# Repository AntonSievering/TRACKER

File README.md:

# TRACKER - Sounding Rocket Tracking and Positioning Project

The rocket carries a transmitter that continuously downlinks telemetry along with timing signals. Multiple ground receivers (3–4 planned) receive the signal and extract the timing information. With the timing data, the system computes the rocket’s position in real time.

This repository contains the PCB projects for TRACKER
- GPSDO-V2: 10 MHz oscillator tuned by the GPS timing signals
  
- basestation-rx: S-band timing signal receiver
  
- tracker-tx-fpga: FPGA baseboard with three subcarrier slots
  
- tracker-subcarrier-adc: ADC subcarrier for FPGA baseboard
  
- tracker-subcarrier-dac: DAC subcarrier for FPGA baseboard
  
- tracker-tx: RF Upconverter for the rocket-side transmitter (untested)

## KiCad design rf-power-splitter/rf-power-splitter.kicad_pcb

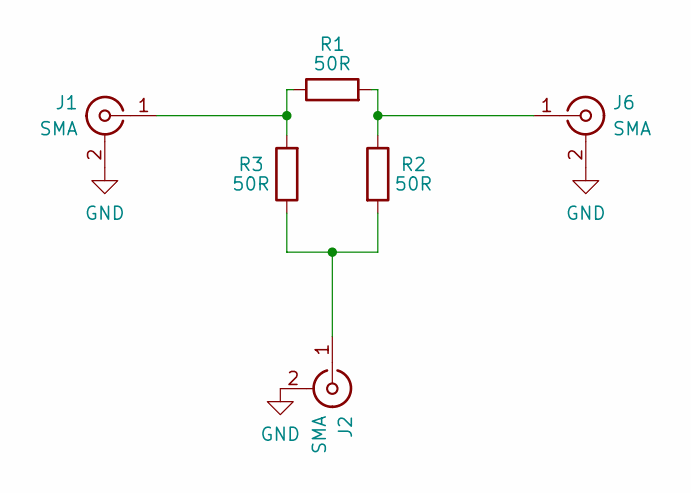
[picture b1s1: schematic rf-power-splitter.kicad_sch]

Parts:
J1, J2, J6: SMA; SMA_Edge_Mount
R1, R2, R3: 50R; R_0402_1005Metric; MPN FC0402E50R0BST1

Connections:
GND: J1.2 (Ext), J2.2 (Ext), J6.2 (Ext)
unnamed: J1.1 (In), R1.1, R3.2
unnamed: J2.1 (In), R2.2, R3.1
unnamed: J6.1 (In), R1.2, R2.1

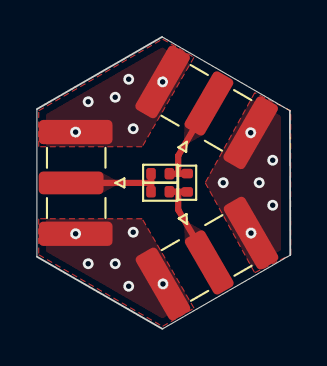
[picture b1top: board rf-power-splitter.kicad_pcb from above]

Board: 4 copper layers, 14.1 x 16.2 mm, 6 parts (0 on the bottom side), 4 nets.

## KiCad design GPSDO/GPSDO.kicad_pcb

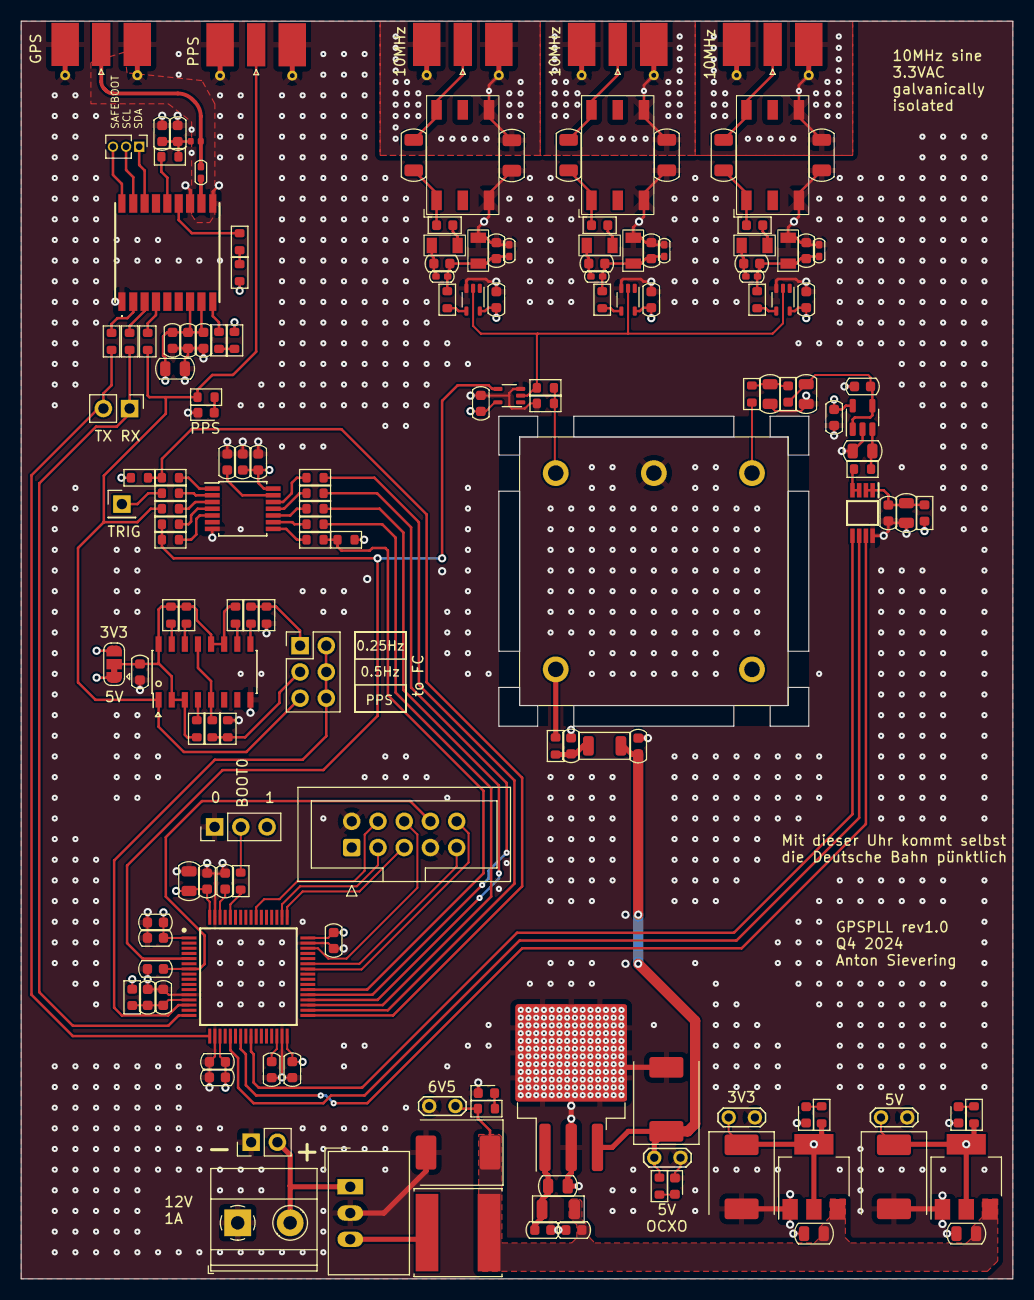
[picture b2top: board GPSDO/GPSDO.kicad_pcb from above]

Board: 4 copper layers, 96.0 x 121.7 mm, 163 parts (0 on the bottom side), 105 nets.

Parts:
C1: 47p; C_0402_1005Metric_Pad0.74x0.62mm
C2: 100p; C_0603_1608Metric
C3: 10n; C_0603_1608Metric
C4, C33, C36, C39, C61, C63: 1u; C_0603_1608Metric
C5, C6, C12, C13, C18, C23, C24, C28, C29, C30, C31, C32, C35, C38, C46, C53, C62, C64: 100n; C_0603_1608Metric
C7, C21, C42, C60: 100u; CP_EIA-7361-438_AVX-U
C8, C10, C11, C25: 470n; C_0603_1608Metric
C9, C15, C16, C17, C19, C20, C22, C34, C41: 10u; C_0805_2012Metric
C14, C48, C55: 470p; C_0402_1005Metric_Pad0.74x0.62mm
C26, C27: 2u2; C_0603_1608Metric
C37, C50, C57: 56p; C_0402_1005Metric_Pad0.74x0.62mm
C40, C43, C47, C49, C54, C56: Tuning; C_0603_1608Metric
C44, C45, C51, C52, C58, C59: 100p; C_1206_3216Metric
D1, D2, D3, D4, D5: LED; LED_0603_1608Metric
FB1, FB2: 600@100MHz; L_1206_3216Metric
FB3, FB4, FB5, FB6, FB7, FB8: 1k@100MHz; L_0603_1608Metric
IC1: MAX-M10S-00B; MAXM10S00B
IC2: STM32H562RGT6; QFP50P1200X1200X160-64N
J1, J7, J8, J9, J12: SMA; SMA_Molex_73251-2120_EdgeMount_Horizontal
J2: Screw_Terminal_01x02; TerminalBlock_Phoenix_MKDS-1,5-2-5.08_1x02_P5.08mm_Horizont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
J3, J13: Conn_01x02_Pin; PinHeader_1x02_P2.54mm_Vertical
J4: Conn_01x03_Pin; PinHeader_1x03_P1.27mm_Vertical
J5: Conn_01x03; PinHeader_1x03_P2.54mm_Vertical
J6: Conn_02x05_Counter_Clockwise; IDC-Header_2x05_P2.54mm_Vertical
J10: Conn_01x01_Pin; PinHeader_1x01_P2.54mm_Vertical
J11: Conn_02x03_Odd_Even; PinHeader_2x03_P2.54mm_Vertical
JP1: SolderJumper_3_Bridged12; SolderJumper-3_P1.3mm_Bridged12_RoundedPad1.0x1.5mm
L1: 27n; L_0402_1005Metric
L2, L4, L6: 560n; NLV25-EF
L3, L5, L7: 4u7; NLV25-EF
L8: 10u; L_Changjiang_FNR8050S
R1, R2, R3, R4, R5: 33R; R_0603_1608Metric
R6, R7, R10, R11, R12, R19, R20, R21, R22, R23, R24, R27, R28, R29, R30, R31, R32, R33, R34: 0; R_0603_1608Metric
R8, R9, R35, R37, R39, R40, R41, R42: 10k; R_0603_1608Metric
R13, R15, R16: 50; R_0603_1608Metric
R14: 1k; R_0603_1608Metric
R17, R18, R25, R26: 100k; R_0603_1608Metric
R36, R38: 20k; R_0603_1608Metric
T1, T2, T3: TG04-APL7NSNL
TP1, TP2, TP3, TP4: TestPoint_2Pole; TestPoint_2Pads_Pitch2.54mm_Drill0.8mm
U1: TSR_1-2465; Converter_DCDC_TRACO_TSR-1_THT
U2: ADC8551; SOP65P490X110-8N
U3: LM1117MP-5.0; SOT-223-3_TabPin2
U4: TL081; SOT-23-5
U5, U7, U8, U9: 74LVC1G17; Texas_R-PDSO-G5_DCK-5
U6: LM1117MP-3.3; SOT-223-3_TabPin2
U10: LM2940; TO-263-3_TabPin2
U11: TDC7200; TSSOP-14_4.4x5mm_P0.65mm
U12: 74VHC112; SOIC-16_3.9x9.9mm_Pitch1.27mm
X1: OC5SC25

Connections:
+3.3V: C4.1, C5.1, C6.1, C12.1, C13.1, C17.1, C28.1, C29.1, C30.1, C31.1, C33.1, C34.1, C38.1, C39.1, C42.1, C46.1, C53.1, C62.1, C63.1, FB8.2, IC1.7 (V_IO), IC1.8 (VCC), IC2.1 (VBAT), IC2.19 (VDD_1), IC2.32 (VDD_2), IC2.48 (VDD_3), IC2.64 (VDD_4), J5.3, J6.1, JP1.3 (B), R17.1, R18.1, R25.1, R26.1, R39.1, TP1.1, U5.5 (VCC), U6.2 (VO), U7.5 (VCC), U8.5 (VCC), U9.5 (VCC), U11.14 (V_{DD})
+5V: C21.1, C24.1, FB7.1, JP1.1 (A), R40.1, TP2.1, U3.2 (VO), U4.5 (V+)
+12V: J2.2, J3.2, U1.1 (Vin)
/DAC/adc_amp+: C22.1, R8.2, U4.3 (+)
/DAC/adc_vdd: C18.1, C19.1, FB7.2, U2.1 (V_{DD}), U2.2 (V_{REF})
/DAC/dac_vout: R8.1, U2.3 (V_{FB}), U2.4 (V_{OUT})
/DAC/vout: C15.1, C23.1, FB3.1, U4.1, U4.4 (-)
/DAC/~SYNC: IC2.25 (PC5), U2.5 (~SYNC)
/GPS/RF: C1.1, J1.1 (In), L1.1
/GPS/gps_lna_en: R5.1, R26.2
/GPS/gps_lna_en_r: IC1.13 (LNA_EN), R5.2
/GPS/gps_pps: J11.5, J12.1 (In), R3.1, R9.1, R28.1, U12.1 (CLK)
/GPS/gps_pps_r: IC1.4 (TIMEPULSE), R3.2
/GPS/gps_rxd: IC2.16 (PA2), J13.1, R2.1
/GPS/gps_rxd_r: IC1.3 (RXD), R2.2
/GPS/gps_scl_tp: IC1.17 (SCL), J4.2
/GPS/gps_sda_tp: IC1.16 (SDA), J4.1
/GPS/gps_txd: IC2.17 (PA3), J13.2, R1.1
/GPS/gps_txd_r: IC1.2 (TXD), R1.2
/GPS/gps_~reset: R4.1, R25.2
/GPS/gps_~reset_r: IC1.9 (RESET_N), R4.2
/GPS/gps_~safeboot: IC1.18 (SAFEBOOT_N), J4.3
/GPS/vcc_rf_r: IC1.14 (VCC_RF), R6.1
/Microcontroller/DAC.MOSI: IC2.23 (PA7), U2.7 (D_{IN})
/Microcontroller/DAC.SCLK: IC2.21 (PA5), U2.6 (SCLK)
/Microcontroller/DEBUG_RX: IC2.43 (PA10), J6.9
/Microcontroller/DEBUG_TX: IC2.42 (PA9), J6.10
/Microcontroller/Divide By Two (Four)/0.5HZ: J11.3, R35.2, R36.1
/Microcontroller/Divide By Two (Four)/0.25HZ: J11.1, R37.2, R38.1
/Microcontroller/Divide By Two (Four)/OUTPUT: IC2.14 (PA0), J11.2, J11.4, J11.6
/Microcontroller/Divide By Two (Four)/jk_supply: C64.1, JP1.2 (C), R31.2, R32.2, R33.1, R34.1, U12.2 (K), U12.3 (J), U12.11 (J), U12.12 (K), U12.16 (V_{cc})
/Microcontroller/JTCK: IC2.49 (PA14), J6.5
/Microcontroller/JTDI: IC2.50 (PA15), J6.3
/Microcontroller/JTDO: IC2.55 (PB3), J6.4
/Microcontroller/JTMS: IC2.46 (PA13), J6.6
/Microcontroller/NRST: C35.1, IC2.7 (NRST), J6.8
/Microcontroller/TDC.MISO: IC2.35 (PB14), R23.2
/Microcontroller/TDC.MOSI: IC2.36 (PB15), R22.2
/Microcontroller/TDC.SCLK: IC2.34 (PB13), R20.2
/Microcontroller/boot0: J5.2, R10.1
/Microcontroller/boot0_r: IC2.60 (BOOT0), R10.2
/Microcontroller/stm32_vdda: C32.1, C36.1, FB8.1, IC2.13 (VDDA)
/Microcontroller/stm_vcap1: C26.1, IC2.30 (VCAP_1)
/Microcontroller/stm_vcap2: C27.1, IC2.62 (VCAP_2)
/OCXO/Output Driver 1/out+: C44.1, J7.1 (In), T1.6 (SB)
/OCXO/Output Driver 1/out-: C45.1, J7.2 (Ext), T1.4 (SA)
/OCXO/Output Driver 2/out+: C51.1, J8.1 (In), T2.6 (SB)
/OCXO/Output Driver 2/out-: C52.1, J8.2 (Ext), T2.4 (SA)
/OCXO/Output Driver 3/out+: C58.1, J9.1 (In), T3.6 (SB)
/OCXO/Output Driver 3/out-: C59.1, J9.2 (Ext), T3.4 (SA)
/OCXO/ocxo_fout: R12.2, U5.2, U7.2, U8.2, U9.2
/OCXO/ocxo_fout_r: R12.1, R14.1, X1.1 (freq)
/OCXO/ocxo_vadj: R7.1, X1.3 (V_{adj})
/OCXO/ocxo_vcc: C11.1, FB1.2, R11.1
/Phase Comparator/tdc_clock: IC2.5 (PH0-OSC_IN), R29.1, R30.1, U7.4
/Phase Comparator/tdc_clock_r: R30.2, U11.5 (CLOCK)
/Phase Comparator/tdc_en: IC2.33 (PB12), R17.2, R19.2
/Phase Comparator/tdc_en_r: R19.1, U11.1 (EN)
/Phase Comparator/tdc_miso_r: R23.1, U11.9 (MISO)
/Phase Comparator/tdc_mosi_r: R22.1, U11.10 (MOSI)
/Phase Comparator/tdc_sclk_r: R20.1, U11.12 (SCLK)
/Phase Comparator/tdc_start_r: R28.2, U11.3 (START)
/Phase Comparator/tdc_stop_r: R29.2, U11.4 (STOP)
/Phase Comparator/tdc_trig: J10.1, R27.1
/Phase Comparator/tdc_trig_r: R27.2, U11.2 (TRIG)
/Phase Comparator/tdc_vreg: C61.1, U11.13 (V_{REG})
/Phase Comparator/tdc_~cs: IC2.37 (PC6), R21.2
/Phase Comparator/tdc_~cs_r: R21.1, U11.11 (~CS)
/Phase Comparator/tdc_~int: IC2.38 (PC7), R18.2, R24.2
/Phase Comparator/tdc_~int_r: R24.1, U11.8 (~INT)
/Power/6V5: C7.1, C8.1, C20.1, C41.1, FB2.1, L8.2, R42.1, TP4.1, U3.3 (VI), U6.3 (VI)
/Power/ocxo_5v: C10.1, C60.1, FB1.1, R41.1, TP3.1, U10.3 (VO)
/Power/ocxo_ldo_vin: C9.1, C25.1, FB2.2, U10.1 (VI)
GND: C2.2, C3.2, C4.2, C5.2, C6.2, C7.2, C8.2, C9.2, C10.2, C11.2, C12.2, C13.2, C14.1, C15.2, C16.2, C17.2, C18.2, C19.2, C20.2, C21.2, C22.2, C23.2, C24.2, C25.2, C26.2, C27.2, C28.2, C29.2, C30.2, C31.2, C32.2, C33.2, C34.2, C35.2, C36.2, C38.2, C39.2, C41.2, C42.2, C43.1, C45.2, C46.2, C47.1, C48.1, C52.2, C53.2, C54.1, C55.1, C59.2, C60.2, C61.2, C62.2, C63.2, C64.2, D1.1 (K), D2.1 (K), D3.1 (K), D4.1 (K), D5.1 (K), IC1.1 (GND_1), IC1.10 (GND_2), IC1.12 (GND_3), IC2.12 (VSSA), IC2.18 (VSS_1), IC2.31 (VSS_2), IC2.47 (VSS_3), IC2.63 (VSS_4), J1.2 (Ext), J2.1, J3.1, J5.1, J6.2, J6.7, J12.2 (Ext), L2.2, L4.2, L6.2, R14.2, R36.2, R38.2, T1.3 (AB), T2.3 (AB), T3.3 (AB), TP1.2, TP2.2, TP3.2, TP4.2, U1.2 (GND), U2.8 (GND), U3.1 (GND), U4.2 (V-), U5.3 (GND), U6.1 (GND), U7.3 (GND), U8.3 (GND), U9.3 (GND), U10.2 (GND), U11.7 (GND), U12.8 (GND), X1.2 (GND)
unnamed: C2.1, C3.1, L1.2, R6.2
unnamed: C14.2, C37.2, C40.2, C43.2, L2.1, R15.2
unnamed: C16.1, FB3.2, R7.2
unnamed: C37.1, C40.1, L3.1
unnamed: C47.2, C48.2, C49.2, C50.2, L4.1, R13.2
unnamed: C49.1, C50.1, L5.1
unnamed: C54.2, C55.2, C56.2, C57.2, L6.1, R16.2
unnamed: C56.1, C57.1, L7.1
unnamed: D1.2 (A), R9.2
unnamed: D2.2 (A), R39.2
unnamed: D3.2 (A), R40.2
unnamed: D4.2 (A), R41.2
unnamed: D5.2 (A), R42.2
unnamed: FB4.1, L3.2
unnamed: FB5.1, L5.2
unnamed: FB6.1, L7.2
unnamed: C1.2, IC1.11 (RF_IN)
unnamed: R13.1, U8.4
unnamed: R15.1, U5.4
unnamed: R16.1, U9.4
unnamed: C44.2, FB4.2, T1.1 (AA)
unnamed: C51.2, FB5.2, T2.1 (AA)
unnamed: C58.2, FB6.2, T3.1 (AA)
unnamed: L8.1, U1.3 (Vout)
unnamed: R35.1, U12.5 (Q), U12.13 (CLK)
unnamed: R33.2, U12.15 (~CLR)
unnamed: R31.1, U12.4 (~PR)
unnamed: R37.1, U12.9 (Q)
unnamed: R34.2, U12.14 (~CLR)
unnamed: R32.1, U12.10 (~PR)
unnamed: R11.2, X1.5 (Vcc)

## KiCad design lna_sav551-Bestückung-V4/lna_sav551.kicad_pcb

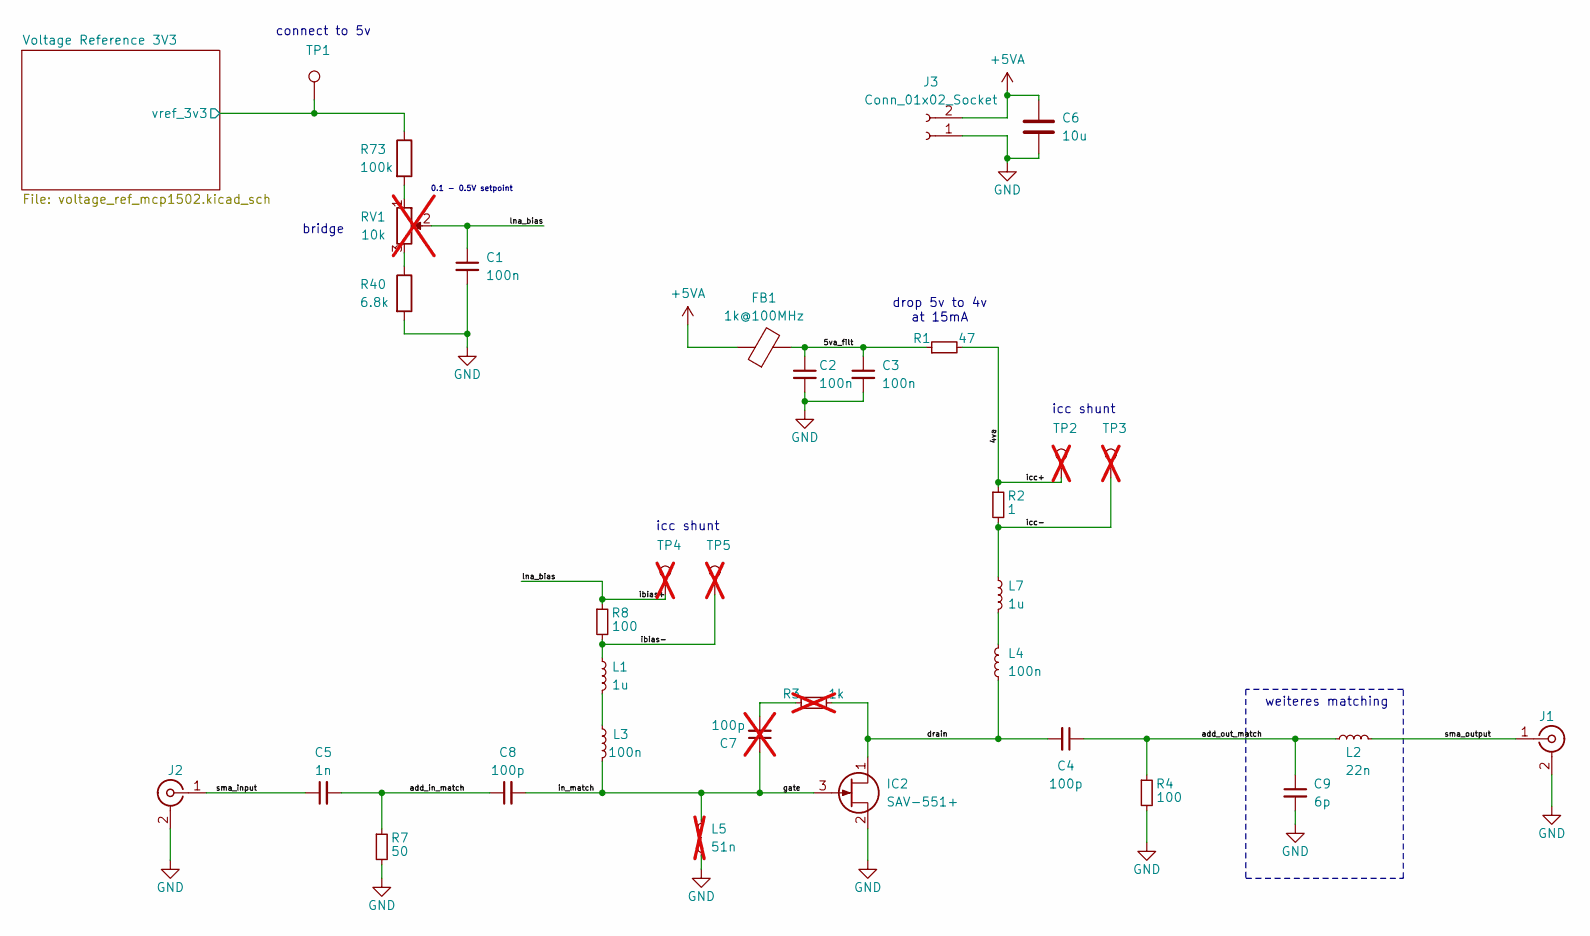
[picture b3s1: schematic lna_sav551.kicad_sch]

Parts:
C1, C2, C3: 100n; R_0603_1608Metric
C4: 100p; R_0603_1608Metric; MPN C0603C471F8HACTU
C5: 1n; R_0603_1608Metric; MPN C0603C150J8HACTU
C6: 10u; R_0805_2012Metric
C7: 100p; R_0603_1608Metric; not fitted
C8: 100p; R_0603_1608Metric; MPN C0603C150J8HACTU
C9: 6p; R_0603_1608Metric; MPN C0603C471F8HACTU
FB1: 1k@100MHz; R_0603_1608Metric; MPN 81-BLM18KG102SH1D
IC2: SAV-551+; SAV551; Manufacturer_Part_Number SAV-551+
J1, J2: SMA; SMA_Edge_Mount
J3: Conn_01x02_Socket; PinHeader_1x02_P2.54mm_Vertical
L1, L7: 1u; L_0805_2012Metric; MPN MCL2012V1-1R0-R
L2: 22n; R_0603_1608Metric; MPN AIMC-0603-82NJ-T
L3, L4: 100n; R_0603_1608Metric; MPN AIMC-0603-82NJ-T
L5: 51n; R_0603_1608Metric; MPN LQW18AN51NG00D; not fitted
R1: 47; R_0603_1608Metric
R2: 1; R_0603_1608Metric
R3: 1k; R_0603_1608Metric; not fitted
R4, R8: 100; R_0603_1608Metric
R7: 50; R_0603_1608Metric
R40: 6.8k; R_0603_1608Metric
R73: 100k; R_0603_1608Metric
RV1: 10k; Potentiometer_Bourns_3386X_Horizontal; MPN PTN10-C10HB20; not fitted
TP1: TestPoint; TestPoint_Pad_D1.0mm
TP2, TP3, TP4, TP5: TestPoint; TestPoint_Pad_D1.0mm; not fitted

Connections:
+5VA: C6.1, FB1.1, J3.2; also elsewhere on the board
/4va: R1.2, R2.1, TP2.1
/5va_filt: C2.1, C3.1, FB1.2, R1.1
/Voltage Reference 3V3/vref_3v3: R73.1, TP1.1; also elsewhere on the board
/add_in_match: C5.2, C8.1, R7.1
/add_out_match: C4.1, C9.1, L2.1, R4.1
/drain: C4.2, IC2.1, L4.1, R3.2
/gate: C7.1, C8.2, IC2.3, L3.1, L5.2
/ibias+: C1.1, R8.1, RV1.2, TP4.1
/ibias-: L1.1, R8.2, TP5.1
/icc-: L7.1, R2.2, TP3.1
/sma_input: C5.1, J2.1 (In)
/sma_output: J1.1 (In), L2.2
GND: C1.2, C2.2, C3.2, C6.2, C9.2, IC2.2, IC2.4 (GND), J1.2 (Ext), J2.2 (Ext), J3.1, L5.1, R4.2, R7.2, R40.2; also elsewhere on the board
unnamed: C7.2, R3.1
unnamed: L1.2, L3.2
unnamed: L4.2, L7.2
unnamed: R40.1, RV1.3
unnamed: R73.2, RV1.1

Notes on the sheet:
weiteres matching
drop 5v to 4v at 15mA
bridge
connect to 5v
0.1 - 0.5V setpoint
icc shunt

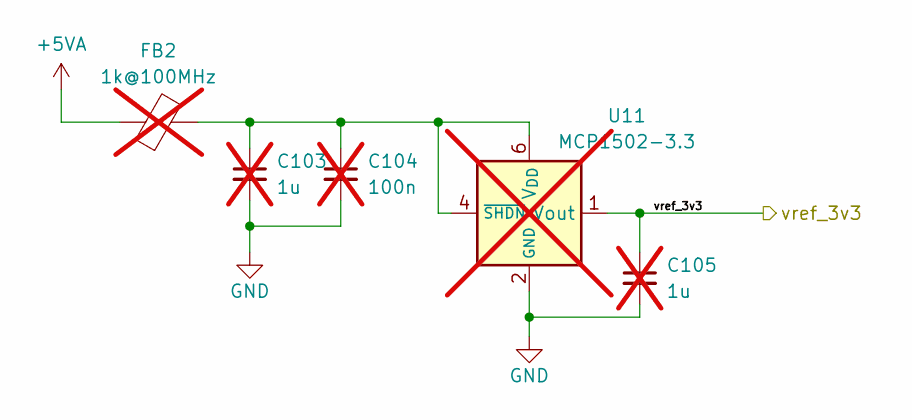
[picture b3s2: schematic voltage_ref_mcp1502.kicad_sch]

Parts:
C103, C105: 1u; R_0603_1608Metric; not fitted
C104: 100n; R_0603_1608Metric; not fitted
FB2: 1k@100MHz; R_0603_1608Metric; MPN 81-BLM18KG102SH1D; not fitted
U11: MCP1502-3.3; TSOT-23-6; MPN 579-MCP1502T-33E/CHY; not fitted

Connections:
+5VA: FB2.1; also elsewhere on the board
/Voltage Reference 3V3/vref_3v3: C105.1, U11.1 (Vout); also elsewhere on the board
GND: C103.2, C104.2, C105.2, U11.2 (GND), U11.3 (GND), U11.5 (GND); also elsewhere on the board
unnamed: C103.1, C104.1, FB2.2, U11.4 (~SHDN), U11.6 (V_{DD})

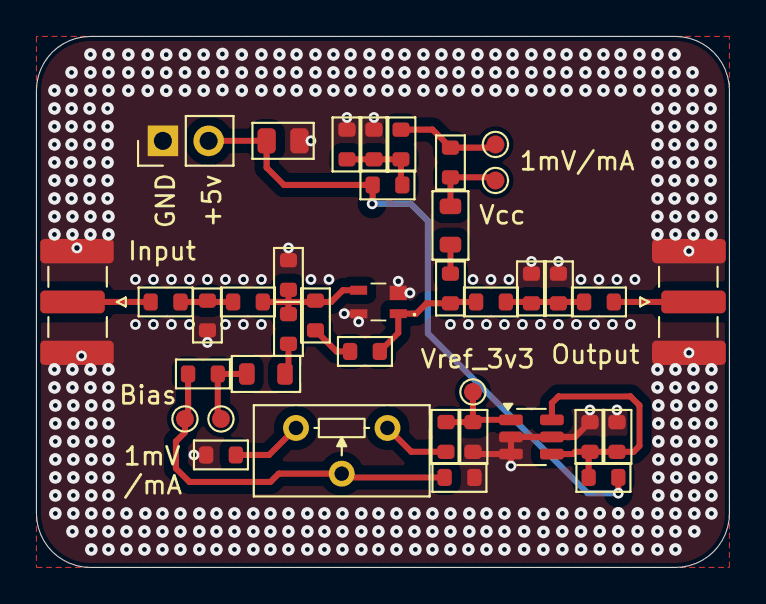
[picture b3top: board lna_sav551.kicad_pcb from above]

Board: 4 copper layers, 38.5 x 29.5 mm, 39 parts (0 on the bottom side), 20 nets.

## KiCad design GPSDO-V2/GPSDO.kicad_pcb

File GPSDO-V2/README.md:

# GPSDO
GPS disciplinated 10MHz oscillator

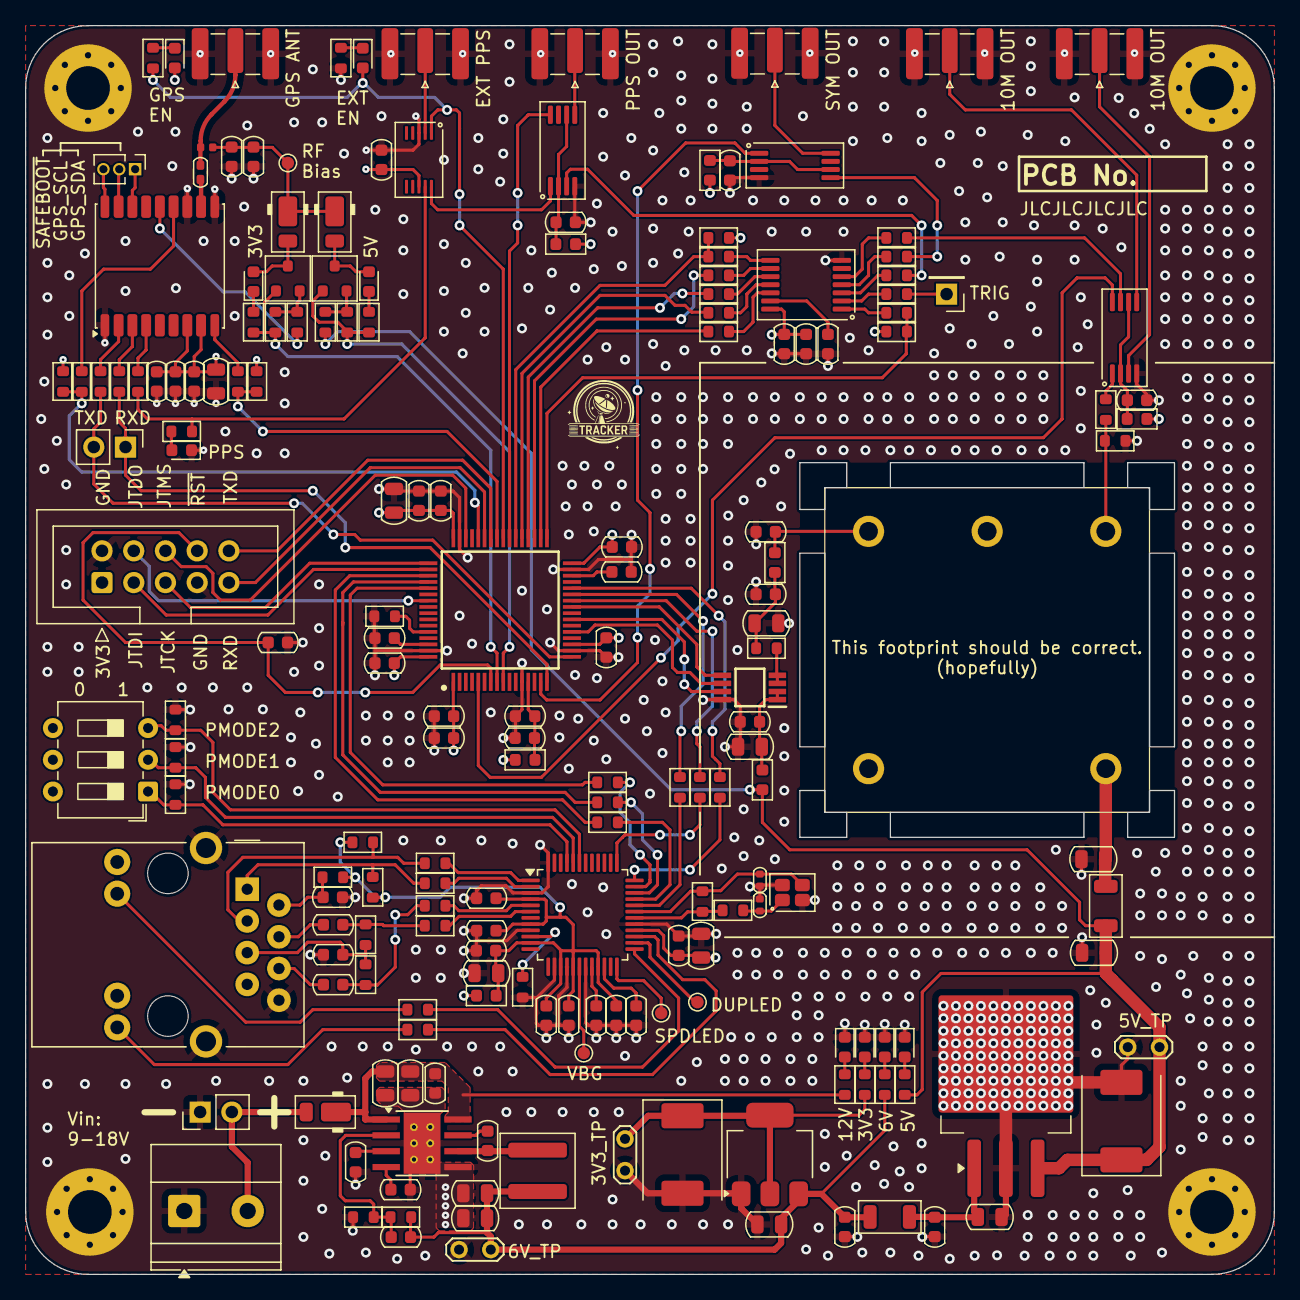
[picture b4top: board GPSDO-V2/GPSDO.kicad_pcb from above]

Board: 4 copper layers, 100.0 x 100.0 mm, 191 parts (0 on the bottom side), 140 nets.

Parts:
C1, C4, C5, C9, C14, C15, C16, C17, C18, C19, C23, C30, C31, C32, C34, C35, C37, C39, C45, C52, C56, C57, C58, C59: 100n; C_0603_1608Metric
C2, C12, C22, C24, C25, C27, C29, C42, C43, C46, C47, C60: 10u; C_0805_2012Metric
C3, C13, C20, C21, C38, C40, C48: 1u; C_0603_1608Metric
C6: 47p; C_0402_1005Metric_Pad0.74x0.62mm
C7, C53: 100p; C_0603_1608Metric
C8, C61, C63: 10n; C_0603_1608Metric
C10, C11: 2u2; C_0603_1608Metric
C26, C28, C41, C44: 470n; C_0603_1608Metric
C33, C36: 18p; C_0402_1005Metric
C49: 3.3n; C_0603_1608Metric
C50, C51: 100u; CP_EIA-7361-438_AVX-U
C54, C55: 22u; C_0805_2012Metric
C62: 4.7u; C_0603_1608Metric
C64: 22n; C_0603_1608Metric
C65, C66: 6.8n; C_0603_1608Metric
D1, D2, D3, D4, D5, D6, D7, D8, D9: LED; LED_0603_1608Metric
D10, D11, D12: DFLS130; D_PowerDI-123
FB1, FB2, FB4, FB5, FB6, FB7, FB9: 1k@100MHz; L_0603_1608Metric
FB3, FB8: 600@100MHz; L_1206_3216Metric
H1, H2, H3, H4: MountingHole_Pad; MountingHole_3.5mm_Pad_Via
IC1: 74LVC2G3157DPJ; TSSOP-10_3x3mm_P0.5mm
IC2: MAX-M10S-00B; ublox_MAX
IC3: STM32H562RGT6; QFP50P1200X1200X160-64N
IC4, IC5, IC6: LMK1C1104PWR; TSSOP-8_4.4x3mm_P0.65mm
J1, J2, J4, J5, J6, J7: SMA; SMA_Edge_Mount
J3: Screw_Terminal_01x02; TerminalBlock_Phoenix_MKDS-1,5-2-5.08_1x02_P5.08mm_Horizont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
J8, J13: Conn_01x02_Pin; PinHeader_1x02_P2.54mm_Vertical
J9: Conn_01x03_Pin; PinHeader_1x03_P1.27mm_Vertical
J10: RJ45_Bel_SI-60062-F
J11: Conn_02x05_Counter_Clockwise; IDC-Header_2x05_P2.54mm_Vertical
J12: Conn_01x01_Pin; PinHeader_1x01_P2.54mm_Vertical
L1: 27n; L_0402_1005Metric
L2: 3.3u; L_Coilcraft_XAL5030
Q1, Q2: DMP3125L; SOT-23
R1, R9, R24, R25: 100k; R_0603_1608Metric
R2, R3, R4, R5, R8: 33R; R_0603_1608Metric
R6, R7, R26, R27, R29, R30, R31, R32, R33, R54, R57, R58, R59, R60, R61: 10k; R_0603_1608Metric
R10, R13, R14, R15, R16, R17, R18, R19, R20, R21, R22, R23, R34, R36, R37, R38, R39, R40, R41, R42, R43, R44, R45, R55, R56: 0; R_0603_1608Metric
R11, R12: 1k; R_0603_1608Metric
R28: 68k; R_0603_1608Metric
R35: 1M; R_0603_1608Metric
R46: 12.4k 1%; R_0603_1608Metric
R47, R48, R49, R50: 50; R_0603_1608Metric
R51: 10; R_0603_1608Metric
R52, R53: 330; R_0603_1608Metric
SW1: SW_DIP_x03; SW_DIP_SPSTx03_Slide_6.7x9.18mm_W7.62mm_P2.54mm_LowProfile
TP1, TP2, TP3: TestPoint_2Pole; TestPoint_2Pads_Pitch2.54mm_Drill0.8mm
TP4, TP5, TP6, TP7: TestPoint; TestPoint_Pad_D1.0mm
U1: DAC8551; SOP65P490X110-8N
U2: TDC7200; TSSOP-14_4.4x5mm_P0.65mm
U3: LM1117MP-3.3; SOT-223-3_TabPin2
U4: LM2940; TO-263-3_TabPin2
U5: BD9D321EFJ; Texas_HTSOP-8-1EP_3.9x4.9mm_P1.27mm_EP2.95x4.9mm_Mask2.4x3.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
U6: W5500; LQFP-48_7x7mm_P0.5mm
X1: OC5SC25
X2: 25M; Crystal_SMD_EuroQuartz_X22-4Pin_2.5x2.0mm

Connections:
+3.3V: C1.1, C2.1, C3.1, C4.1, C5.1, C12.1, C13.1, C14.1, C15.1, C16.1, C17.1, C18.1, C20.1, C38.1, C39.1, C50.1, C59.1, C60.1, D8.2 (A), FB1.2, FB5.2, FB6.2, FB7.2, FB9.2, IC1.8 (VCC), IC2.7 (V_IO), IC2.8 (VCC), IC3.1 (VBAT), IC3.19 (VDD_1), IC3.32 (VDD_2), IC3.48 (VDD_3), IC3.64 (VDD_4), J10.L1, J10.L3, J11.1, R1.1, R9.1, R24.1, R25.1, R26.1, SW1.4, SW1.5, SW1.6, TP1.1, U2.14 (V_{DD}), U3.2 (VO), U6.28 (VDD)
+3.3VA: C29.1, C30.1, C32.1, C35.1, C56.1, C57.1, C58.1, FB9.1, R48.1, R50.1, R51.1, U6.4 (AVDD), U6.8 (AVDD), U6.11 (AVDD), U6.15 (AVDD), U6.17 (AVDD), U6.21 (AVDD)
+12V: C42.1, C43.1, C45.1, D10.1 (K), R54.1, U5.1 (EN), U5.8 (VIN)
/10M Distribution/CLK_{1}: IC4.3 (Y0), J7.1 (In)
/10M Distribution/CLK_{2}: IC3.5 (PH0-OSC_IN), IC4.8 (Y1)
/10M Distribution/CLK_{3}: IC4.5 (Y2), J5.1 (In)
/10M Distribution/clk_buf_vcc: C31.1, FB5.1, IC4.2 (1G), IC4.6 (VDD)
/DAC/adc_antialias: C24.1, C26.1, FB4.1, R11.2
/DAC/adc_vdd: C22.1, C23.1, FB2.2, U1.1 (V_{DD}), U1.2 (V_{REF})
/DAC/dac_rect: R11.1, U1.3 (V_{FB}), U1.4 (V_{OUT})
/DAC/~SYNC: IC3.25 (PC5), U1.5 (~SYNC)
/Ethernet/ACTLED: R52.2, U6.27 (ACTLED)
/Ethernet/LINKLED: R53.2, U6.25 (LINKLED)
/Ethernet/MISO: IC3.52 (PC11), R38.1
/Ethernet/MOSI: IC3.53 (PC12), R39.1
/Ethernet/SCLK: IC3.51 (PC10), R37.1
/Ethernet/rj45_rct: C63.1, J10.5 (RCT), R47.2, R49.2
/Ethernet/rj45_rd+: C65.2, J10.4 (RD+)
/Ethernet/rj45_rd-: C66.2, J10.6 (RD-)
/Ethernet/rj45_tct: C64.1, J10.2 (TCT), R51.2
/Ethernet/rj45_td+: J10.1 (TD+), R43.2, R50.2
/Ethernet/rj45_td-: J10.3 (TD-), R42.2, R48.2
/Ethernet/~CS: IC3.27 (PB1), R36.1
/Ethernet/~INT: IC3.28 (PB2), R40.1
/Ethernet/~RST: IC3.26 (PB0), R41.1
/GPS/3v3_BIAS_EN: IC3.8 (PC0), Q1.1 (G), R7.2, R58.2
/GPS/5v_BIAS_EN: IC3.9 (PC1), Q2.1 (G), R57.2, R59.2
/GPS/RF: C6.1, J1.1 (In), L1.1
/GPS/gps_lna_en: IC3.44 (PA11), R8.1, R9.2
/GPS/gps_lna_en_r: IC2.13 (LNA_EN), R8.2
/GPS/gps_pps: IC1.9 (1Y0), R3.1, R6.1
/GPS/gps_pps_r: IC2.4 (TIMEPULSE), R3.2
/GPS/gps_rxd: IC3.16 (PA2), J8.1, R5.1
/GPS/gps_rxd_r: IC2.3 (RXD), R5.2
/GPS/gps_scl_tp: IC2.17 (SCL), J9.2
/GPS/gps_sda_tp: IC2.16 (SDA), J9.1
/GPS/gps_txd: IC3.17 (PA3), J8.2, R4.1
/GPS/gps_txd_r: IC2.2 (TXD), R4.2
/GPS/gps_~reset: IC3.41 (PA8), R1.2, R2.1
/GPS/gps_~reset_r: IC2.9 (RESET_N), R2.2
/GPS/gps_~safeboot: IC2.18 (SAFEBOOT_N), J9.3
/GPS/rf_bias: C7.1, C8.1, D11.1 (K), D12.1 (K), L1.2, TP7.1
/GPS/vcc_rf_r: IC2.14 (VCC_RF), R55.1
/Microcontroller/DAC.MOSI: IC3.23 (PA7), U1.7 (D_{IN})
/Microcontroller/DAC.SCLK: IC3.21 (PA5), U1.6 (SCLK)
/Microcontroller/DEBUG_RX: IC3.43 (PA10), J11.9
/Microcontroller/DEBUG_TX: IC3.42 (PA9), J11.10
/Microcontroller/JTCK: IC3.49 (PA14), J11.5
/Microcontroller/JTDI: IC3.50 (PA15), J11.3
/Microcontroller/JTDO: IC3.55 (PB3), J11.4
/Microcontroller/JTMS: IC3.46 (PA13), J11.6
/Microcontroller/NRST: C9.1, IC3.7 (NRST), J11.8
/Microcontroller/PC8: IC3.39 (PC8), IC6.8 (Y1)
/Microcontroller/PC9: D9.2 (A), IC1.1 (1S), IC3.40 (PC9), R60.2
/Microcontroller/TDC.MISO: IC3.35 (PB14), R22.2
/Microcontroller/TDC.MOSI: IC3.36 (PB15), R21.2
/Microcontroller/TDC.SCLK: IC3.34 (PB13), R19.2
/Microcontroller/boot0_r: IC3.60 (BOOT0), R10.2
/Microcontroller/stm32_vdda: C19.1, C21.1, FB1.1, IC3.13 (VDDA)
/Microcontroller/stm_vcap1: C10.1, IC3.30 (VCAP_1)
/Microcontroller/stm_vcap2: C11.1, IC3.62 (VCAP_2)
/OCXO/ocxo_fout: IC4.1 (CLKIN), R13.2
/OCXO/ocxo_fout_r: R12.1, R13.1, X1.1 (freq)
/OCXO/ocxo_vadj: C28.1, FB4.2, X1.3 (V_{adj})
/OCXO/ocxo_vcc: C27.1, FB3.2, X1.5 (Vcc)
/PC_STOP: IC5.5 (Y2), R16.1
/PPS Distribution/CLK_{3}: IC6.5 (Y2), J4.1 (In)
/PPS Distribution/REFIN: IC1.10 (1Z), IC6.1 (CLKIN)
/PPS Distribution/clk_buf_vcc: C37.1, FB7.1, IC6.2 (1G), IC6.6 (VDD)
/Phase Comparator/tdc_clock: IC4.7 (Y3), R17.1
/Phase Comparator/tdc_clock_r: R17.2, U2.5 (CLOCK)
/Phase Comparator/tdc_en: IC3.33 (PB12), R18.2, R24.2
/Phase Comparator/tdc_en_r: R18.1, U2.1 (EN)
/Phase Comparator/tdc_miso_r: R22.1, U2.9 (MISO)
/Phase Comparator/tdc_mosi_r: R21.1, U2.10 (MOSI)
/Phase Comparator/tdc_sclk_r: R19.1, U2.12 (SCLK)
/Phase Comparator/tdc_start: IC6.3 (Y0), R15.1
/Phase Comparator/tdc_start_r: R15.2, U2.3 (START)
/Phase Comparator/tdc_stop_r: R16.2, U2.4 (STOP)
/Phase Comparator/tdc_trig: J12.1, R14.1
/Phase Comparator/tdc_trig_r: R14.2, U2.2 (TRIG)
/Phase Comparator/tdc_vreg: C40.1, U2.13 (V_{REG})
/Phase Comparator/tdc_~cs: IC3.37 (PC6), R20.2
/Phase Comparator/tdc_~cs_r: R20.1, U2.11 (~CS)
/Phase Comparator/tdc_~int: IC3.38 (PC7), R23.2, R25.2
/Phase Comparator/tdc_~int_r: R23.1, U2.8 (~INT)
/Power/DCDC_6v: C41.1, C46.1, C53.1, C54.1, C55.1, FB8.1, L2.2, R28.1, R30.1, TP3.1, U3.3 (VI)
/Power/POWER+: D10.2 (A), J3.2, J13.2
/Power/ocxo_5v: C25.1, C51.1, FB2.1, FB3.1, R27.1, R56.1, TP2.1, U4.3 (VO)
/Power/ocxo_ldo_vin: C44.1, C47.1, FB8.2, U4.1 (VI)
/Symbol Distribution/CLK_{2}: IC5.8 (Y1), J6.1 (In)
/Symbol Distribution/clk_buf_vcc: C34.1, FB6.1, IC5.2 (1G), IC5.6 (VDD)
/stm_divider_output: IC3.15 (PA1), IC5.1 (CLKIN)
GND: C1.2, C2.2, C3.2, C4.2, C5.2, C7.2, C8.2, C9.2, C10.2, C11.2, C12.2, C13.2, C14.2, C15.2, C16.2, C17.2, C18.2, C19.2, C20.2, C21.2, C22.2, C23.2, C24.2, C25.2, C26.2, C27.2, C28.2, C29.2, C30.2, C31.2, C32.2, C33.2, C34.2, C35.2, C36.2, C37.2, C38.2, C39.2, C40.2, C41.2, C42.2, C43.2, C44.2, C45.2, C46.2, C47.2, C48.2, C49.2, C50.2, C51.2, C54.2, C55.2, C56.2, C57.2, C58.2, C59.2, C60.2, C61.2, C62.2, C63.2, C64.2, D1.1 (K), D2.1 (K), D3.1 (K), D4.1 (K), D5.1 (K), H1.1, H2.1, H3.1, H4.1, IC1.3 (GND), IC2.1 (GND_1), IC2.10 (GND_2), IC2.12 (GND_3), IC3.12 (VSSA), IC3.18 (VSS_1), IC3.31 (VSS_2), IC3.47 (VSS_3), IC3.63 (VSS_4), IC4.4 (GND), IC5.4 (GND), IC6.4 (GND), J1.2 (Ext), J2.2 (Ext), J3.1, J4.2 (Ext), J5.2 (Ext), J6.2 (Ext), J7.2 (Ext), J10.8, J10.SH, J11.2, J11.7, J13.1, R10.1, R12.2, R29.2, R31.1, R32.1, R33.1, R46.2, R61.2, TP1.2, TP2.2, TP3.2, U1.8 (GND), U2.7 (GND), U3.1 (GND), U4.2 (GND), U5.5 (GND), U5.9 (GND), U6.3 (AGND), U6.9 (AGND), U6.14 (AGND), U6.16 (AGND), U6.19 (AGND), U6.29 (GND), U6.48 (AGND), X1.2 (GND), X2.2, X2.4
unnamed: C33.1, R34.1, X2.1
unnamed: C65.1, R45.2, R47.1
unnamed: C66.1, R44.2, R49.1
unnamed: D1.2 (A), R6.2
unnamed: D2.2 (A), R26.2
unnamed: D3.2 (A), R27.2
unnamed: D4.2 (A), R30.2
unnamed: D5.2 (A), R54.2
unnamed: D6.1 (K), R7.1
unnamed: D7.1 (K), R59.1
unnamed: D8.1 (K), R60.1
unnamed: D9.1 (K), R61.1
unnamed: D7.2 (A), D11.2 (A), Q2.3 (D)
unnamed: D6.2 (A), D12.2 (A), Q1.3 (D)
unnamed: IC1.2 (1Y1), J2.1 (In)
unnamed: C6.2, IC2.11 (RF_IN)
unnamed: J10.L2, R53.1
unnamed: J10.L4, R52.1
unnamed: Q1.2 (S), R55.2, R58.1
unnamed: Q2.2 (S), R56.2, R57.1
unnamed: C52.1, U5.7 (BOOT)
unnamed: C53.2, R28.2, R29.1, U5.2 (FB)
unnamed: C49.1, U5.4 (SS)
unnamed: C52.2, L2.1, U5.6 (SW)
unnamed: C48.1, U5.3 (VREG)
unnamed: C61.1, U6.22 (1V2O)
unnamed: TP6.1, U6.26 (DUPLED)
unnamed: R46.1, U6.10 (EXRES1)
unnamed: R38.2, U6.34 (MISO)
unnamed: R39.2, U6.35 (MOSI)
unnamed: R33.2, SW1.1, U6.45 (PMODE0)
unnamed: R32.2, SW1.2, U6.44 (PMODE1)
unnamed: R31.2, SW1.3, U6.43 (PMODE2)
unnamed: R44.1, U6.5 (RXN)
unnamed: R45.1, U6.6 (RXP)
unnamed: R37.2, U6.33 (SCLK)
unnamed: TP5.1, U6.24 (SPDLED)
unnamed: C62.1, U6.20 (TOCAP)
unnamed: R42.1, U6.1 (TXN)
unnamed: R43.1, U6.2 (TXP)
unnamed: TP4.1, U6.18 (VBG)
unnamed: R34.2, R35.1, U6.30 (XI/CLKIN)
unnamed: C36.1, R35.2, U6.31 (XO), X2.3
unnamed: R40.2, U6.36 (~INT)
unnamed: R41.2, U6.37 (~RST)
unnamed: R36.2, U6.32 (~SCS)
